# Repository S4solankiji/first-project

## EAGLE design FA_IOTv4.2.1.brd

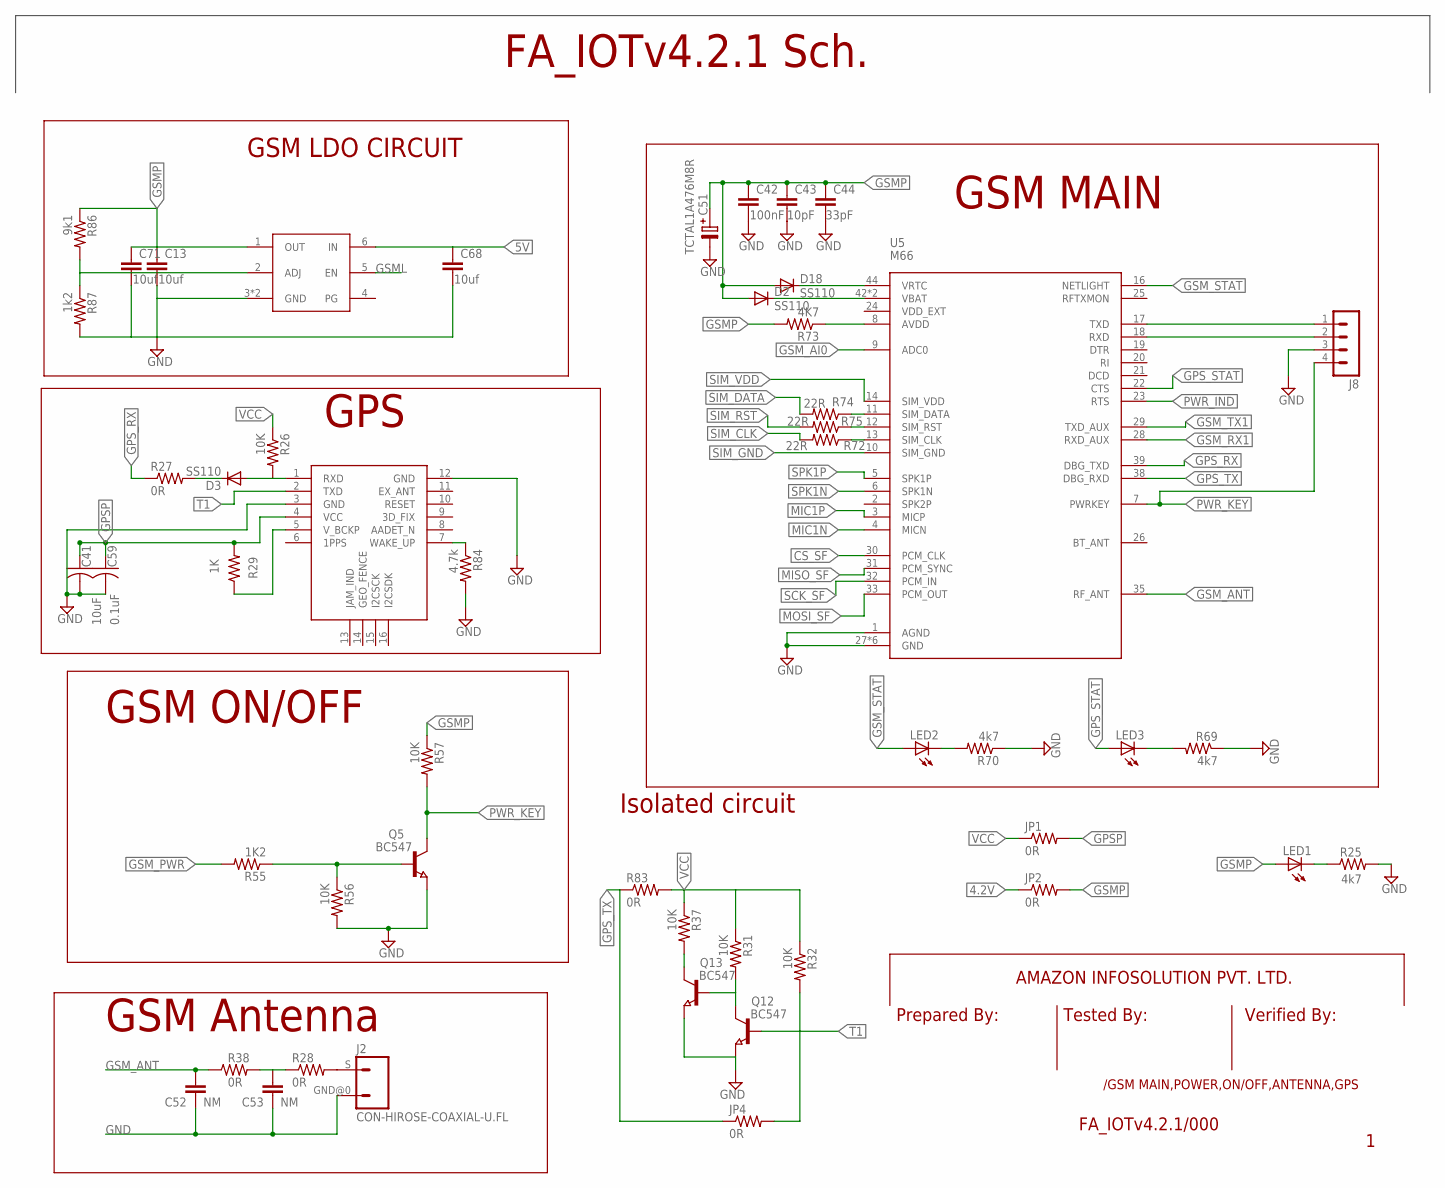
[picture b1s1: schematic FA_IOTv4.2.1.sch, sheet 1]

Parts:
C13, C68, C71: 10uf; C0805
C41: 10uF; C0805
C42: 100nF; C0805
C43: 10pF; C0805
C44: 33pF; C0805
C51: TCTAL1A476M8R; TE-A-3216
C52, C53: NM; C0402
C59: 0.1uF; C0402
D2, D3, D18: SS110; DO-214AC
J2: CON-HIROSE-COAXIAL-U.FL; CON-U.FL
J8: MA04-1
JP1, JP2, JP4: 0R; R0805
LED1, LED2, LED3: LEDCHIP-LED0805; CHIP-LED0805
Q5, Q12, Q13: BC547; SOT23
R25, R69, R70: 4k7; R0402
R26, R31, R32, R37, R56, R57: 10K; R0402
R27, R83: 0R; R0805
R28, R38: 0R; R0402
R29: 1K; R0402
R55: 1K2; R0402
R72, R74, R75: 22R; R0402
R73: 4K7; R0402
R84: 4.7k; R0402
R86: 9k1; R0402
R87: 1k2; R0402
U5: M66
U$1: L89
U$3: LD39200PU33R; SON95P300X300X100-7N

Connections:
4.2V: JP2.1; also elsewhere on the board
5V: C68.1, U$3.6 (IN); also elsewhere on the board
CS_SF: U5.30 (PCM_CLK); also elsewhere on the board
GND: C13.2, C41.2, C42.2, C43.2, C44.2, C51.-, C52.2, C53.2, C59.2, C68.2, C71.2, J2.GND@0 (2), J8.3, Q5.2 (E), Q12.2 (E), Q13.2 (E), R25.2, R56.2, R69.1, R70.1, R84.2, R87.2, U5.1 (AGND), U5.27 (GND), U5.34 (GND), U5.36 (GND), U5.37 (GND), U5.40 (GND), U5.41 (GND), U$1.3 (GND), U$1.12 (GND), U$3.3 (GND), U$3.7 (GND); also elsewhere on the board
GPSP: C41.1, C59.1, JP1.2, R29.2, U$1.4 (VCC); also elsewhere on the board
GPS_RX: R27.1, U5.39 (DBG_TXD)
GPS_STAT: LED3.A, U5.22 (CTS)
GPS_TX: JP4.1, R83.1, U5.38 (DBG_RXD)
GSML: U$3.5 (EN); also elsewhere on the board
GSMP: C13.1, C42.1, C43.1, C44.1, C51.+, C71.1, D2.A, D18.A, JP2.2, LED1.A, R57.1, R73.2, R86.1, U$3.1 (OUT); also elsewhere on the board
GSM_AI0: U5.9 (ADC0); also elsewhere on the board
GSM_ANT: C52.1, R38.1, U5.35 (RF_ANT)
GSM_PWR: R55.2; also elsewhere on the board
GSM_RX1: U5.28 (RXD_AUX); also elsewhere on the board
GSM_STAT: LED2.A, U5.16 (NETLIGHT)
GSM_TX1: U5.29 (TXD_AUX); also elsewhere on the board
MIC1N: U5.4 (MICN); also elsewhere on the board
MIC1P: U5.3 (MICP); also elsewhere on the board
MISO_SF: U5.31 (PCM_SYNC); also elsewhere on the board
MOSI_SF: U5.33 (PCM_OUT); also elsewhere on the board
unnamed: Q13.3 (C), R37.2
unnamed: D2.C, U5.42 (VBAT), U5.43 (VBAT)
unnamed: J2.S (1), R28.2
unnamed: R29.1, U$1.5 (V_BCKP)
unnamed: D3.A, R26.2, U$1.1 (RXD)
unnamed: D3.C, R27.2
unnamed: Q12.3 (C), Q13.1 (B), R31.2
unnamed: Q5.1 (B), R55.1, R56.1
unnamed: R84.1, U$1.7 (WAKE_UP)
unnamed: LED1.C, R25.1
unnamed: LED3.C, R69.2
unnamed: LED2.C, R70.2
unnamed: R73.1, U5.8 (AVDD)
unnamed: R74.1, U5.11 (SIM_DATA)
unnamed: D18.C, U5.44 (VRTC)
unnamed: R75.1, U5.12 (SIM_RST)
unnamed: R72.1, U5.13 (SIM_CLK)
unnamed: R86.2, R87.1, U$3.2 (ADJ)
PWR_IND: U5.23 (RTS); also elsewhere on the board
PWR_KEY: J8.4, Q5.3 (C), R57.2, U5.7 (PWRKEY)
RF_ANT: C53.1, R28.1, R38.2
RX_DEBUG: J8.2, U5.18 (RXD)
SCK_SF: U5.32 (PCM_IN); also elsewhere on the board
SIM_CLK: R72.2; also elsewhere on the board
SIM_DATA: R74.2; also elsewhere on the board
SIM_GND: U5.10 (SIM_GND); also elsewhere on the board
SIM_RST: R75.2; also elsewhere on the board
SIM_VDD: U5.14 (SIM_VDD); also elsewhere on the board
SPK1N: U5.6 (SPK1N); also elsewhere on the board
SPK1P: U5.5 (SPK1P); also elsewhere on the board
T1: JP4.2, Q12.1 (B), R32.2, U$1.2 (TXD)
TX_DEBUG: J8.1, U5.17 (TXD)
VCC: JP1.1, R26.1, R31.1, R32.1, R37.1, R83.2; also elsewhere on the board

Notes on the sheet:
GSM ON/OFF
GPS
GSM MAIN
GSM Antenna
AMAZON INFOSOLUTION PVT. LTD.
Prepared By:
Tested By:
Verified By:
/GSM MAIN,POWER,ON/OFF,ANTENNA,GPS
FA_IOTv4.2.1/000
FA_IOTv4.2.1 Sch.
GSM LDO CIRCUIT
Isolated circuit

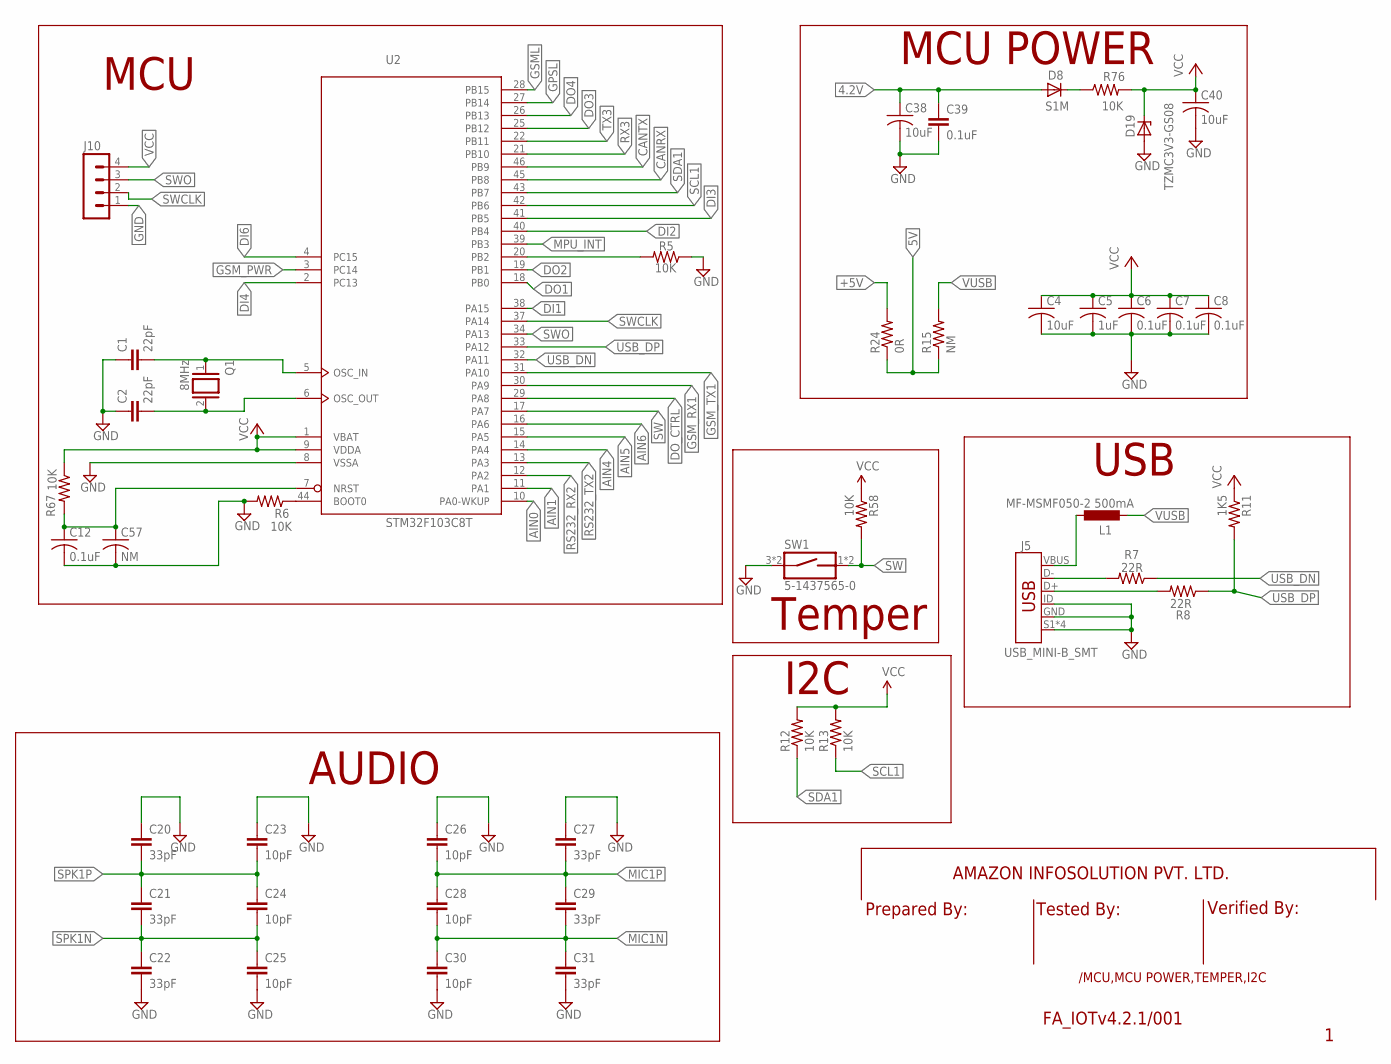
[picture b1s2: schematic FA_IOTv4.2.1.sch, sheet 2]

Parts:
C1, C2: 22pF; C0201
C4, C38, C40: 10uF; C0805
C5: 1uF; C0603
C6, C7, C8, C12: 0.1uF; C0402
C20, C21, C22, C27, C29, C31: 33pF; C0402
C23, C24, C25, C26, C28, C30: 10pF; C0402
C39: 0.1uF; C0805
C57: NM; C0402
D8: S1M; DO-214AC
D19: TZMC3V3-GS08; SOD80C
J5: USB_MINI-B_SMT; USB-MINIB
J10: MA04-1
L1: MF-MSMF050-2 500mA; L1812
Q1: 8MHz; QS
R5, R6, R58, R67: 10K; R0402
R7, R8: 22R; R0402
R11: 1K5; R0402
R12, R13: 10K; 0603-RES
R15: NM; R0805
R24: 0R; R0805
R76: 10K; R0805
SW1: 5-1437565-0; SW_5-1437565-0
U2: STM32F103C8T; LQFP48

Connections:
4.2V: C38.1, C39.1, D8.A; also elsewhere on the board
5V: R15.1, R24.1; also elsewhere on the board
+5V: R24.2; also elsewhere on the board
AIN0: U2.10 (PA0-WKUP); also elsewhere on the board
AIN1: U2.11 (PA1); also elsewhere on the board
AIN4: U2.14 (PA4); also elsewhere on the board
AIN5: U2.15 (PA5)
AIN6: U2.16 (PA6)
CANRX: U2.45 (PB8); also elsewhere on the board
CANTX: U2.46 (PB9); also elsewhere on the board
DI1: U2.38 (PA15); also elsewhere on the board
DI2: U2.40 (PB4); also elsewhere on the board
DI3: U2.41 (PB5); also elsewhere on the board
DI4: U2.2 (PC13)
DI6: U2.4 (PC15); also elsewhere on the board
DO1: U2.18 (PB0); also elsewhere on the board
DO2: U2.19 (PB1); also elsewhere on the board
DO3: U2.25 (PB12); also elsewhere on the board
DO4: U2.26 (PB13); also elsewhere on the board
DO_CTRL: U2.29 (PA8)
GND: C1.1, C2.1, C4.2, C5.2, C6.2, C7.2, C8.2, C12.2, C20.1, C22.2, C23.1, C25.2, C26.1, C27.1, C30.2, C31.2, C38.2, C39.2, C40.2, C57.2, D19.A, J5.GND, J5.ID, J5.S1 (SHIELD), J5.S2 (SHIELD), J5.S3 (SHIELD), J5.S4 (SHIELD), J10.1, R5.1, R6.2, SW1.3 (1), SW1.4 (1), U2.8 (VSSA), U2.23 (GND), U2.35 (GND), U2.47 (GND); also elsewhere on the board
GPSL: U2.27 (PB14); also elsewhere on the board
GSML: U2.28 (PB15); also elsewhere on the board
GSM_PWR: U2.3 (PC14); also elsewhere on the board
GSM_RX1: U2.30 (PA9); also elsewhere on the board
GSM_TX1: U2.31 (PA10); also elsewhere on the board
MIC1N: C28.2, C29.2, C30.1, C31.1; also elsewhere on the board
MIC1P: C26.2, C27.2, C28.1, C29.1; also elsewhere on the board
MPU_INT: U2.39 (PB3); also elsewhere on the board
unnamed: C1.2, Q1.1, U2.5 (OSC_IN)
unnamed: C2.2, Q1.2, U2.6 (OSC_OUT)
unnamed: R6.1, U2.44 (BOOT0)
unnamed: R5.2, U2.20 (PB2)
unnamed: J5.D-, R7.2
unnamed: J5.D+, R8.2
unnamed: J5.VBUS, L1.1
unnamed: D8.C, R76.1
unnamed: C12.1, C57.1, R67.2, U2.7 (NRST)
RS232_RX2: U2.12 (PA2); also elsewhere on the board
RS232_TX2: U2.13 (PA3); also elsewhere on the board
RX3: U2.21 (PB10); also elsewhere on the board
SCL1: R13.1, U2.42 (PB6); also elsewhere on the board
SDA1: R12.1, U2.43 (PB7); also elsewhere on the board
SPK1N: C21.2, C22.1, C24.2, C25.1; also elsewhere on the board
SPK1P: C20.2, C21.1, C23.2, C24.1; also elsewhere on the board
SW: R58.2, SW1.1 (2), SW1.2, U2.17 (PA7)
SWCLK: J10.2, U2.37 (PA14)
SWO: J10.3, U2.34 (PA13)
TX3: U2.22 (PB11); also elsewhere on the board
USB_DN: R7.1, U2.32 (PA11)
USB_DP: R8.1, R11.2, U2.33 (PA12)
VCC: C4.1, C5.1, C6.1, C7.1, C8.1, C40.1, D19.C, J10.4, R11.1, R12.2, R13.2, R58.1, R67.1, R76.2, U2.1 (VBAT), U2.9 (VDDA), U2.24 (VCC), U2.36 (VCC), U2.48 (VCC); also elsewhere on the board
VUSB: L1.2, R15.2

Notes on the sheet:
MCU
MCU POWER
USB
I2C
Temper
AUDIO
AMAZON INFOSOLUTION PVT. LTD.
Prepared By:
Tested By:
Verified By:
/MCU,MCU POWER,TEMPER,I2C
FA_IOTv4.2.1/001

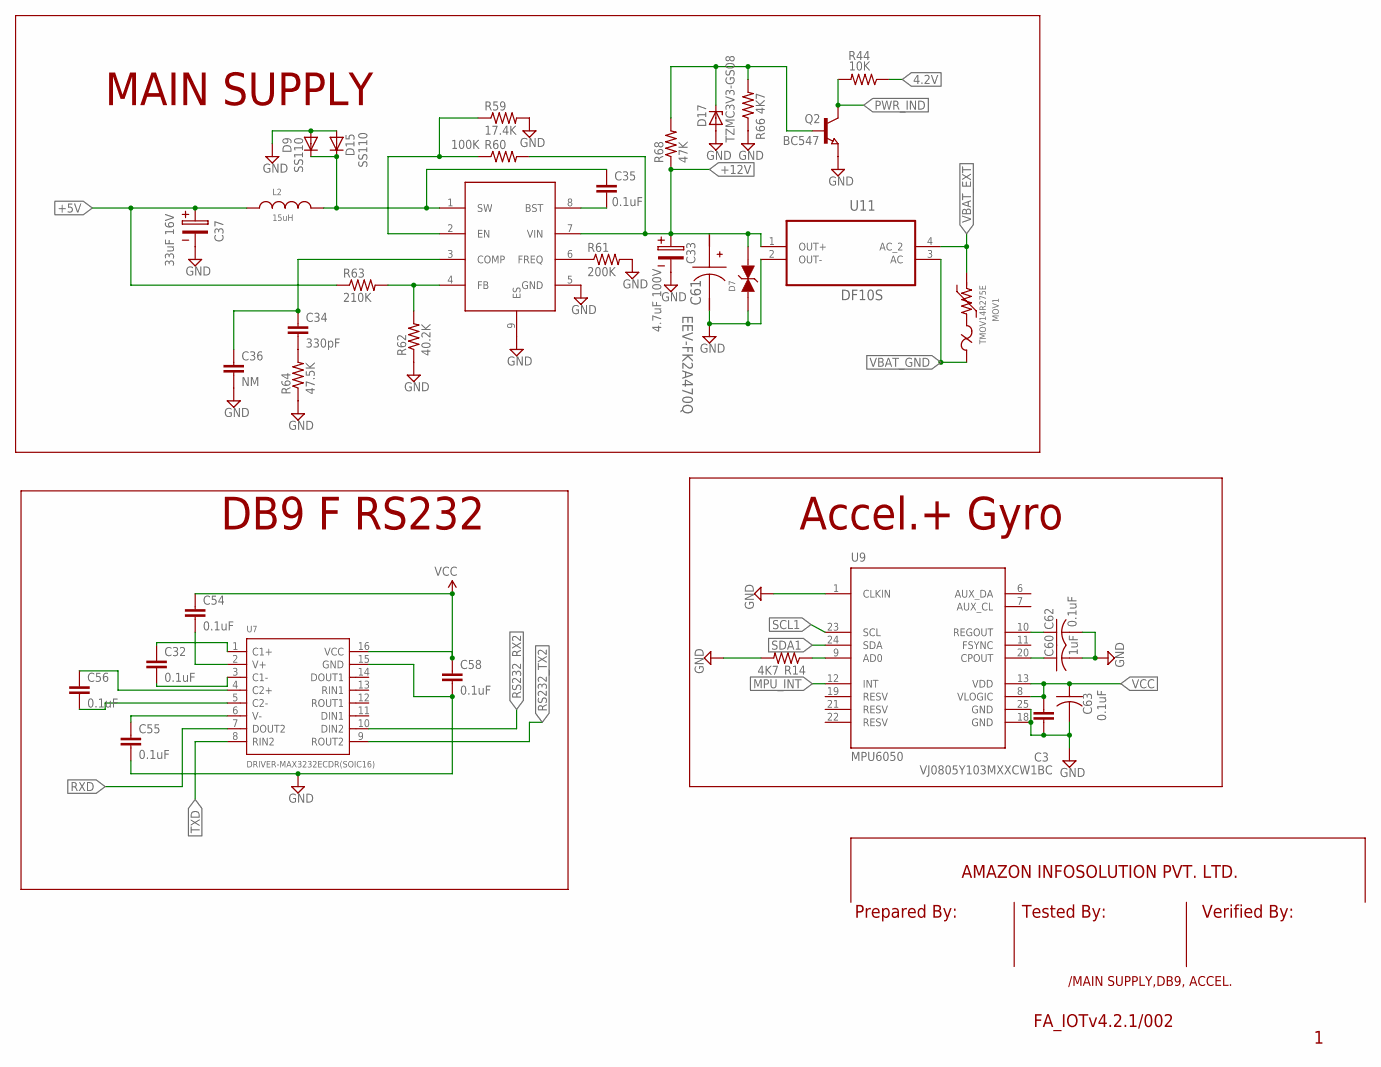
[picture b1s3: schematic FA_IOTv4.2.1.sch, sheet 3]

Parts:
C3: VJ0805Y103MXXCW1BC; C0805
C32, C54, C55, C56, C58, C62, C63: 0.1uF; C0402
C33: 4.7uF 100V; 3.5X1.6X2.1(BXCXA)
C34: 330pF; C0805
C35: 0.1uF; C0805
C36: NM; C0805
C37: 33uF 16V; 3.5X1.6X2.1(BXCXA)
C60: 1uF; C0603
C61: EEV-FK2A470Q; SM_RADIAL_H13
D7: WE-TVSP_BI_1500W_824541331; VARTVSP_SMC&SMD/DO-214AB
D9, D15: SS110; DO-214AC
D17: TZMC3V3-GS08; SOD80C
L2: 15uH; WE-PD_1260/1245/1280/1210
MOV1: TMOV14R275E
Q2: BC547; SOT23
R14: 4K7; R0402
R44: 10K; R0805
R59: 17.4K; R0805
R60: 100K; R0805
R61: 200K; R0805
R62: 40.2K; R0805
R63: 210K; R0805
R64: 47.5K; R0805
R66: 4K7; R0805
R68: 47K; R0805
U7: DRIVER-MAX3232ECDR(SOIC16); SOIC16-1.27-10X3.9MM
U9: MPU6050; QFN50P400X400X95-25T265X275N
U10: MP4559DN; SOIC127P600X170-9N
U11: DF10S; SOT508P985X260-4N

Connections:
4.2V: R44.1; also elsewhere on the board
+5V: C37.1, L2.1, R63.1; also elsewhere on the board
+12V: C33.1, C61.1 (+), D7.2, R60.2, R68.1, U10.7 (VIN), U11.1 (OUT+); also elsewhere on the board
GND: C3.2, C33.2, C36.2, C37.2, C55.2, C58.2, C60.2, C61.2 (-), C62.2, C63.2, D7.1, D9.A, D15.A, D17.A, Q2.2 (E), R14.2, R59.2, R61.2, R62.1, R64.1, R66.1, U7.15 (GND), U9.1 (CLKIN), U9.18 (GND), U9.25 (GND), U10.5 (GND), U10.9 (ES), U11.2 (OUT-); also elsewhere on the board
MPU_INT: U9.12 (INT); also elsewhere on the board
unnamed: C35.1, D9.C, D15.C, L2.2, U10.1 (SW)
unnamed: R14.1, U9.9 (AD0)
unnamed: C62.1, U9.10 (REGOUT)
unnamed: C32.1, U7.1 (C1+)
unnamed: C32.2, U7.3 (C1-)
unnamed: C60.1, U9.20 (CPOUT)
unnamed: R59.1, R60.1, U10.2 (EN)
unnamed: C34.2, R64.2
unnamed: R61.1, U10.6 (FREQ)
unnamed: R62.2, R63.2, U10.4 (FB)
unnamed: C34.1, C36.1, U10.3 (COMP)
unnamed: C35.2, U10.8 (BST)
unnamed: D17.C, Q2.1 (B), R66.2, R68.2
unnamed: C54.2, U7.2 (V+)
unnamed: C56.1, U7.4 (C2+)
unnamed: C56.2, U7.5 (C2-)
unnamed: C55.1, U7.6 (V-)
PWR_IND: Q2.3 (C), R44.2; also elsewhere on the board
RS232_RX2: U7.10 (DIN2); also elsewhere on the board
RS232_TX2: U7.9 (ROUT2); also elsewhere on the board
RXD: U7.7 (DOUT2); also elsewhere on the board
SCL1: U9.23 (SCL); also elsewhere on the board
SDA1: U9.24 (SDA); also elsewhere on the board
TXD: U7.8 (RIN2); also elsewhere on the board
VBAT_EXT: MOV1.2 (MOV), U11.4 (AC_2); also elsewhere on the board
VBAT_GND: MOV1.1 (FUSE), U11.3 (AC); also elsewhere on the board
VCC: C3.1, C54.1, C58.1, C63.1, U7.16 (VCC), U9.8 (VLOGIC), U9.13 (VDD); also elsewhere on the board

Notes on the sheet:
MAIN SUPPLY
DB9 F RS232
Accel.+ Gyro
AMAZON INFOSOLUTION PVT. LTD.
Prepared By:
Tested By:
Verified By:
/MAIN SUPPLY,DB9, ACCEL.
FA_IOTv4.2.1/002

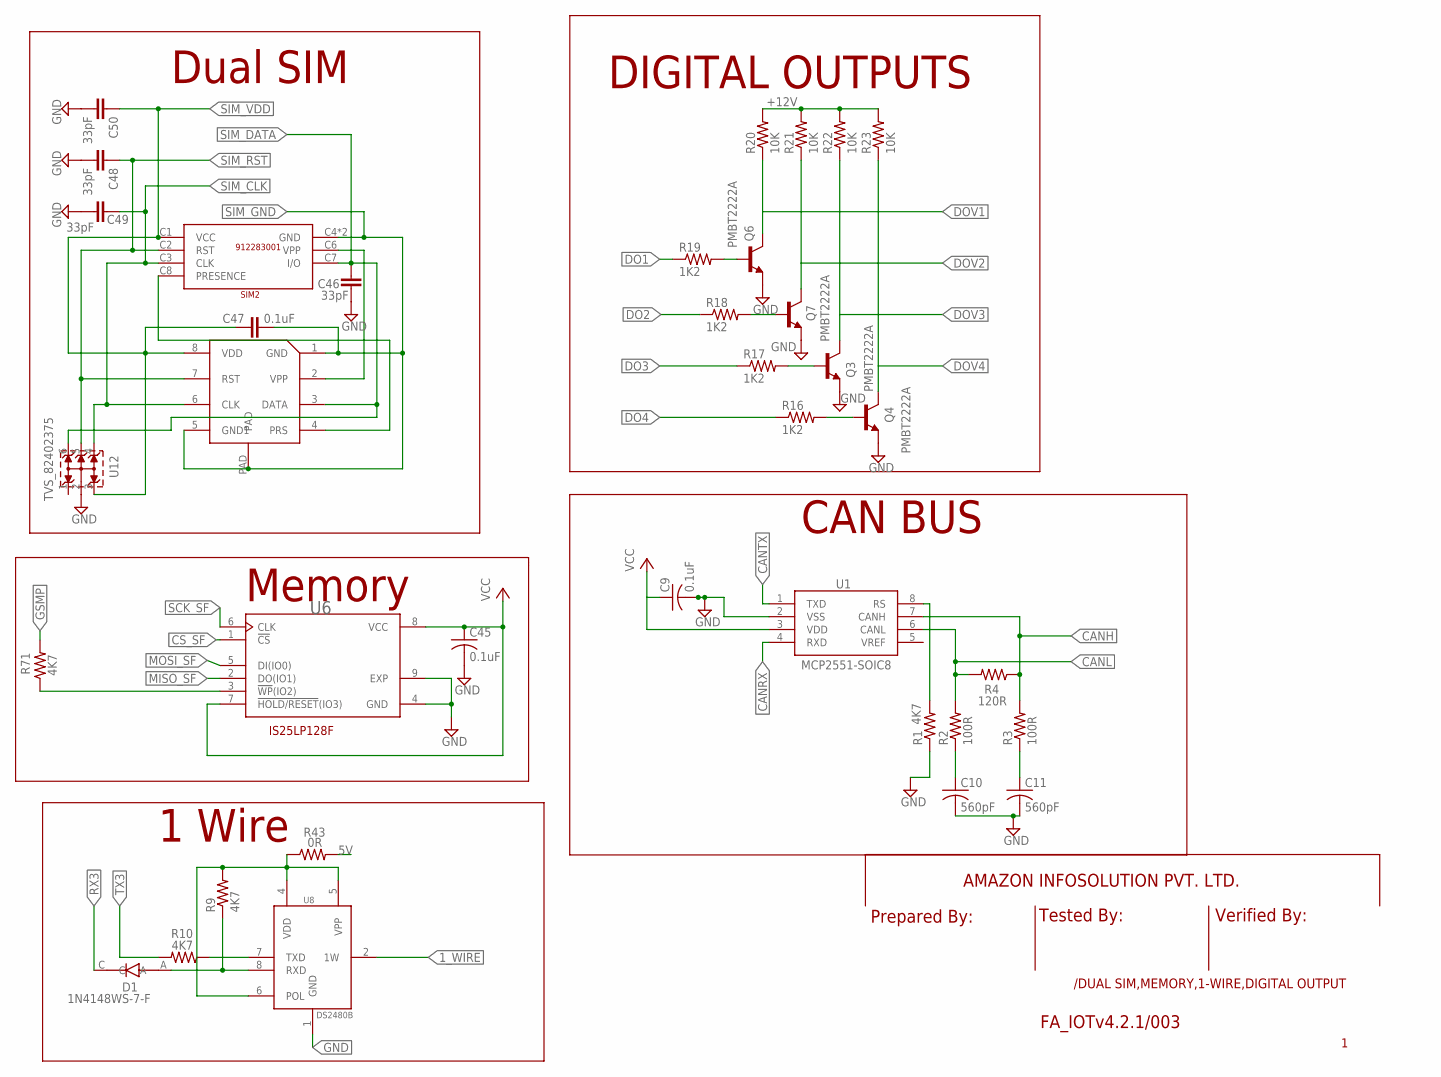
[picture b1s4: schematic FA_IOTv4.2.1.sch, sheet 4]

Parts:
C9, C47: 0.1uF; C0805
C10, C11: 560pF; C0402
C45: 0.1uF; C0402
C46, C48, C49, C50: 33pF; C0805
D1: 1N4148WS-7-F; SOD2513X120N
Q3, Q4, Q6, Q7: PMBT2222A; SOT23-BEC
R1, R9, R10, R71: 4K7; R0402
R2, R3: 100R; R0402
R4: 120R; R0402
R16, R17, R18, R19: 1K2; R0402
R20, R21, R22, R23: 10K; R0805
R43: 0R; R0805
SIM1: MFF2_SIM; MFF2DFN8
SIM2: 912283001; 91228-3001
U1: MCP2551-SOIC8; SOIC8-6.0
U6: W25Q32FVZPIG_TR; SON127P600X500X80-9N
U8: DS2480B; SO08
U12: TVS_82402375; WE-TVS_SC70-6L

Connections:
1_WIRE: U8.2 (1W); also elsewhere on the board
5V: R43.2; also elsewhere on the board
+12V: R20.2, R21.2, R22.2, R23.2; also elsewhere on the board
CANH: R3.2, R4.1, U1.7 (CANH); also elsewhere on the board
CANL: R2.2, R4.2, U1.6 (CANL); also elsewhere on the board
CANRX: U1.4 (RXD); also elsewhere on the board
CANTX: U1.1 (TXD); also elsewhere on the board
CS_SF: U6.1 (!CS); also elsewhere on the board
DO1: R19.1; also elsewhere on the board
DO2: R18.1; also elsewhere on the board
DO3: R17.1; also elsewhere on the board
DO4: R16.1; also elsewhere on the board
DOV1: Q6.C, R20.1; also elsewhere on the board
DOV2: Q7.C, R21.1; also elsewhere on the board
DOV3: Q3.C, R22.1; also elsewhere on the board
DOV4: Q4.C, R23.1; also elsewhere on the board
GND: C9.2, C10.2, C11.2, C45.2, C46.2, C48.2, C49.2, C50.2, Q3.E, Q4.E, Q6.E, Q7.E, R1.1, U1.2 (VSS), U6.4 (GND), U6.9 (EXP), U8.1 (GND), U12.2 (GND); also elsewhere on the board
GSMP: R71.2; also elsewhere on the board
MISO_SF: U6.2 (DO(IO1)); also elsewhere on the board
MOSI_SF: U6.5 (DI(IO0)); also elsewhere on the board
unnamed: C10.1, R2.1
unnamed: C11.1, R3.1
unnamed: R1.2, U1.8 (RS)
unnamed: R10.1, U8.7 (TXD)
unnamed: D1.A, R9.1, U8.8 (RXD)
unnamed: Q6.B, R19.2
unnamed: Q7.B, R18.2
unnamed: Q3.B, R17.2
unnamed: Q4.B, R16.2
unnamed: R9.2, R43.1, U8.4 (VDD), U8.5 (VPP), U8.6 (POL)
unnamed: R71.1, U6.3 (!WP!(IO2))
unnamed: SIM1.4 (PRS), SIM2.C8 (PRESENCE)
unnamed: SIM1.2 (VPP), SIM2.C6 (VPP)
RX3: D1.C; also elsewhere on the board
SCK_SF: U6.6 (CLK); also elsewhere on the board
SIM_CLK: C49.1, SIM1.6 (CLK), SIM2.C3 (CLK), U12.4 (3); also elsewhere on the board
SIM_DATA: C46.1, SIM1.3 (DATA), SIM2.C7 (I/O), U12.6 (5); also elsewhere on the board
SIM_GND: C47.2, SIM1.1 (GND), SIM1.5 (GND1), SIM1.PAD, SIM2.C4 (GND), SIM2.C5 (GND); also elsewhere on the board
SIM_RST: C48.1, SIM1.7 (RST), SIM2.C2 (RST), U12.5 (4); also elsewhere on the board
SIM_VDD: C47.1, C50.1, SIM1.8 (VDD), SIM2.C1 (VCC), U12.3 (2); also elsewhere on the board
TX3: R10.2; also elsewhere on the board
VCC: C9.1, C45.1, U1.3 (VDD), U6.7 (!HOLD/RESET!(IO3)), U6.8 (VCC); also elsewhere on the board

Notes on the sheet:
Dual SIM
DIGITAL OUTPUTS
CAN BUS
Memory
1 Wire
AMAZON INFOSOLUTION PVT. LTD.
Prepared By:
Tested By:
Verified By:
/DUAL SIM,MEMORY,1-WIRE,DIGITAL OUTPUT
FA_IOTv4.2.1/003
IS25LP128F

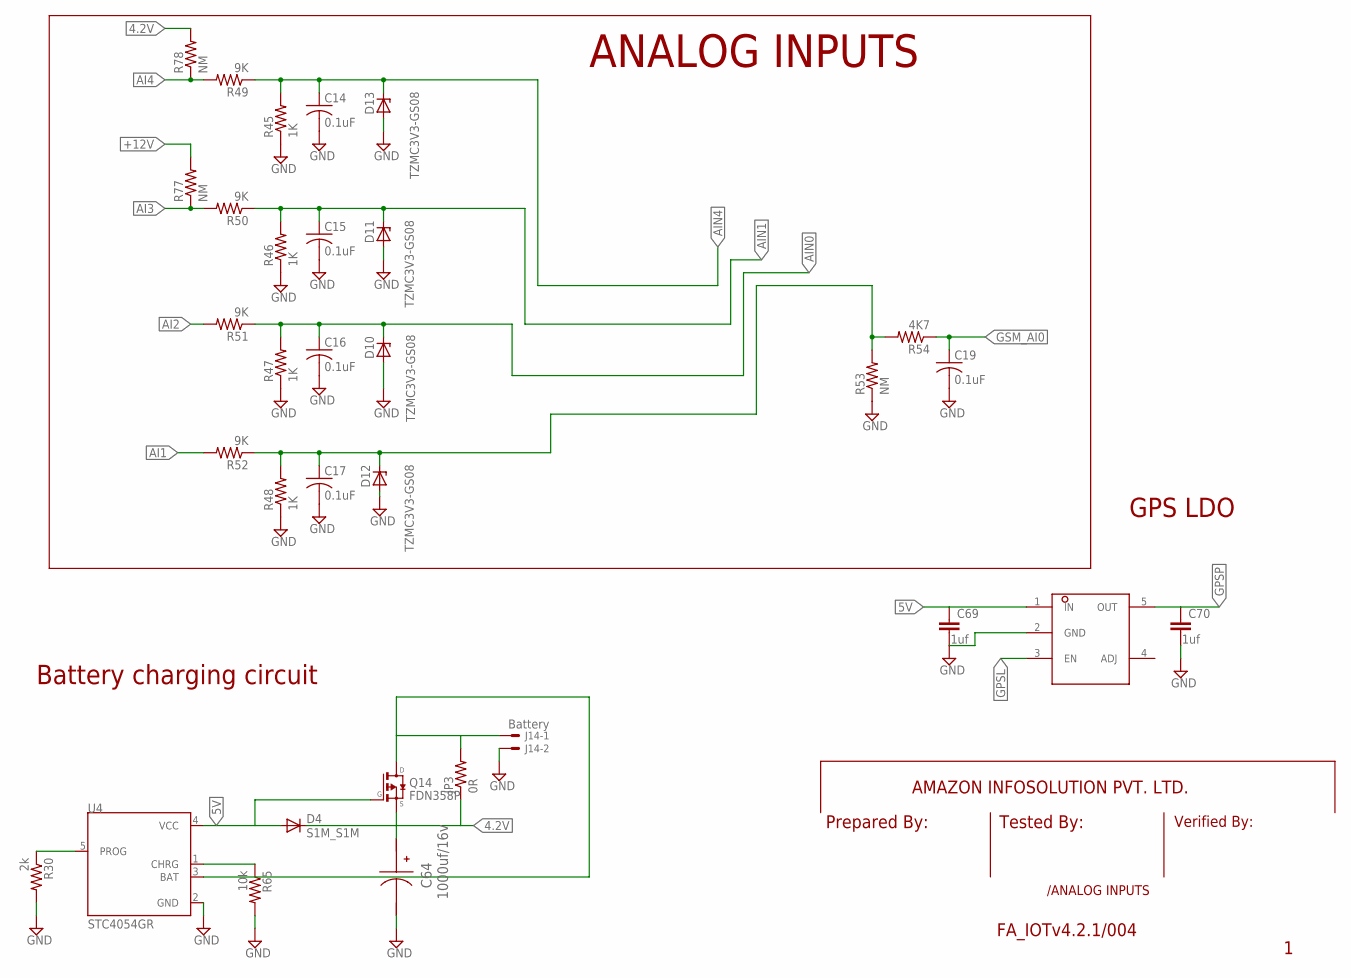
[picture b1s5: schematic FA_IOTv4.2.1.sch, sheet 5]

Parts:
C14, C15, C16, C17, C19: 0.1uF; C0402
C64: 1000uf/16v; SM_RADIAL_H13
C69, C70: 1uf; C0603
D4: S1M_S1M; S1M_DO-214AC
D10, D11, D12, D13: TZMC3V3-GS08; SOD80C
J14: Battery; 6410-02
JP3: 0R; R0805
Q14: FDN358P; SSOT-3
R30: 2k; R0402
R45, R46, R47, R48: 1K; R0402
R49, R50, R51, R52: 9K; R0402
R53: NM; R0402
R54: 4K7; R0402
R65: 10k; R0402
R77, R78: NM; R0805
U4: STC4054GR; SOT95P280X110-5N
U$4: LDK220M33R; SOT95P280X145-5N

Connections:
4.2V: C64.1 (+), D4.C, JP3.1, Q14.2 (S), R78.2; also elsewhere on the board
5V: C69.1, D4.A, Q14.1 (G), U4.4 (VCC), U$4.1 (IN); also elsewhere on the board
+12V: R77.2; also elsewhere on the board
AI1: R52.2; also elsewhere on the board
AI2: R51.2; also elsewhere on the board
AI3: R50.2, R77.1; also elsewhere on the board
AI4: R49.2, R78.1; also elsewhere on the board
AIN0: C16.1, D10.C, R47.2, R51.1; also elsewhere on the board
AIN1: C15.1, D11.C, R46.2, R50.1; also elsewhere on the board
AIN4: C14.1, D13.C, R45.2, R49.1; also elsewhere on the board
FB4: C17.1, D12.C, R48.2, R52.1, R53.2, R54.2
GND: C14.2, C15.2, C16.2, C17.2, C19.2, C64.2 (-), C69.2, C70.2, D10.A, D11.A, D12.A, D13.A, J14.2, R30.2, R45.1, R46.1, R47.1, R48.1, R53.1, R65.2, U4.2 (GND), U$4.2 (GND); also elsewhere on the board
GPSL: U$4.3 (EN); also elsewhere on the board
GPSP: C70.1, U$4.5 (OUT); also elsewhere on the board
GSM_AI0: C19.1, R54.1; also elsewhere on the board
unnamed: J14.1, JP3.2, Q14.3 (D), U4.3 (BAT)
unnamed: R65.1, U4.1 (CHRG)
unnamed: R30.1, U4.5 (PROG)

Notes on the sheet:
ANALOG INPUTS
AMAZON INFOSOLUTION PVT. LTD.
Prepared By:
Tested By:
Verified By:
/ANALOG INPUTS
FA_IOTv4.2.1/004
Battery charging circuit
GPS LDO

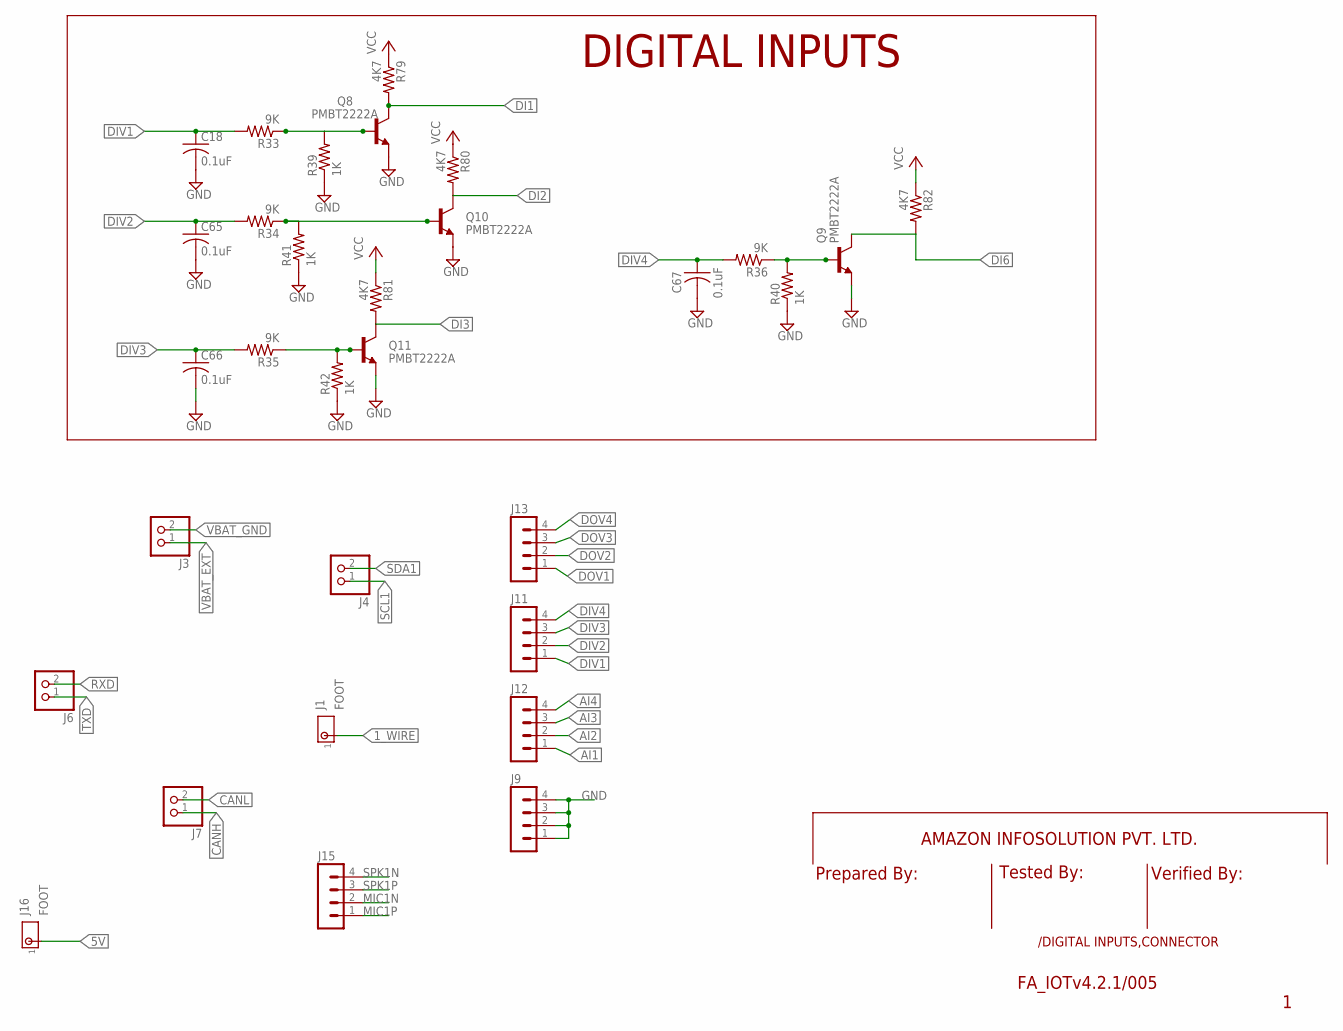
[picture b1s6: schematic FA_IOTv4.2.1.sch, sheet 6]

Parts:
C18, C65, C66, C67: 0.1uF; C0402
J1, J16: FOOT
J3, J4, J6, J7: PINHD-1X2; 1X02
J9, J11, J12, J13, J15: MA04-1
Q8, Q9, Q10, Q11: PMBT2222A; SOT23-BEC
R33, R34, R35, R36: 9K; R0402
R39, R40, R41, R42: 1K; R0402
R79, R80, R81, R82: 4K7; R0402

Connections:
1_WIRE: J1.1; also elsewhere on the board
5V: J16.1; also elsewhere on the board
AI1: J12.1; also elsewhere on the board
AI2: J12.2; also elsewhere on the board
AI3: J12.3; also elsewhere on the board
AI4: J12.4; also elsewhere on the board
CANH: J7.1; also elsewhere on the board
CANL: J7.2; also elsewhere on the board
DI1: Q8.C, R79.2; also elsewhere on the board
DI2: Q10.C, R80.2; also elsewhere on the board
DI3: Q11.C, R81.2; also elsewhere on the board
DI6: Q9.C, R82.2; also elsewhere on the board
DIV1: C18.1, J11.1, R33.2
DIV2: C65.1, J11.2, R34.2
DIV3: C66.1, J11.3, R35.2
DIV4: C67.1, J11.4, R36.2
DOV1: J13.1; also elsewhere on the board
DOV2: J13.2; also elsewhere on the board
DOV3: J13.3; also elsewhere on the board
DOV4: J13.4; also elsewhere on the board
GND: C18.2, C65.2, C66.2, C67.2, J9.1, J9.2, J9.3, J9.4, Q8.E, Q9.E, Q10.E, Q11.E, R39.1, R40.1, R41.1, R42.1; also elsewhere on the board
MIC1N: J15.2; also elsewhere on the board
MIC1P: J15.1; also elsewhere on the board
unnamed: Q8.B, R33.1, R39.2
unnamed: Q9.B, R36.1, R40.2
unnamed: Q10.B, R34.1, R41.2
unnamed: Q11.B, R35.1, R42.2
RXD: J6.2; also elsewhere on the board
SCL1: J4.1; also elsewhere on the board
SDA1: J4.2; also elsewhere on the board
SPK1N: J15.4; also elsewhere on the board
SPK1P: J15.3; also elsewhere on the board
TXD: J6.1; also elsewhere on the board
VBAT_EXT: J3.1; also elsewhere on the board
VBAT_GND: J3.2; also elsewhere on the board
VCC: R79.1, R80.1, R81.1, R82.1; also elsewhere on the board

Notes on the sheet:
DIGITAL INPUTS
AMAZON INFOSOLUTION PVT. LTD.
Prepared By:
Tested By:
Verified By:
/DIGITAL INPUTS,CONNECTOR
FA_IOTv4.2.1/005

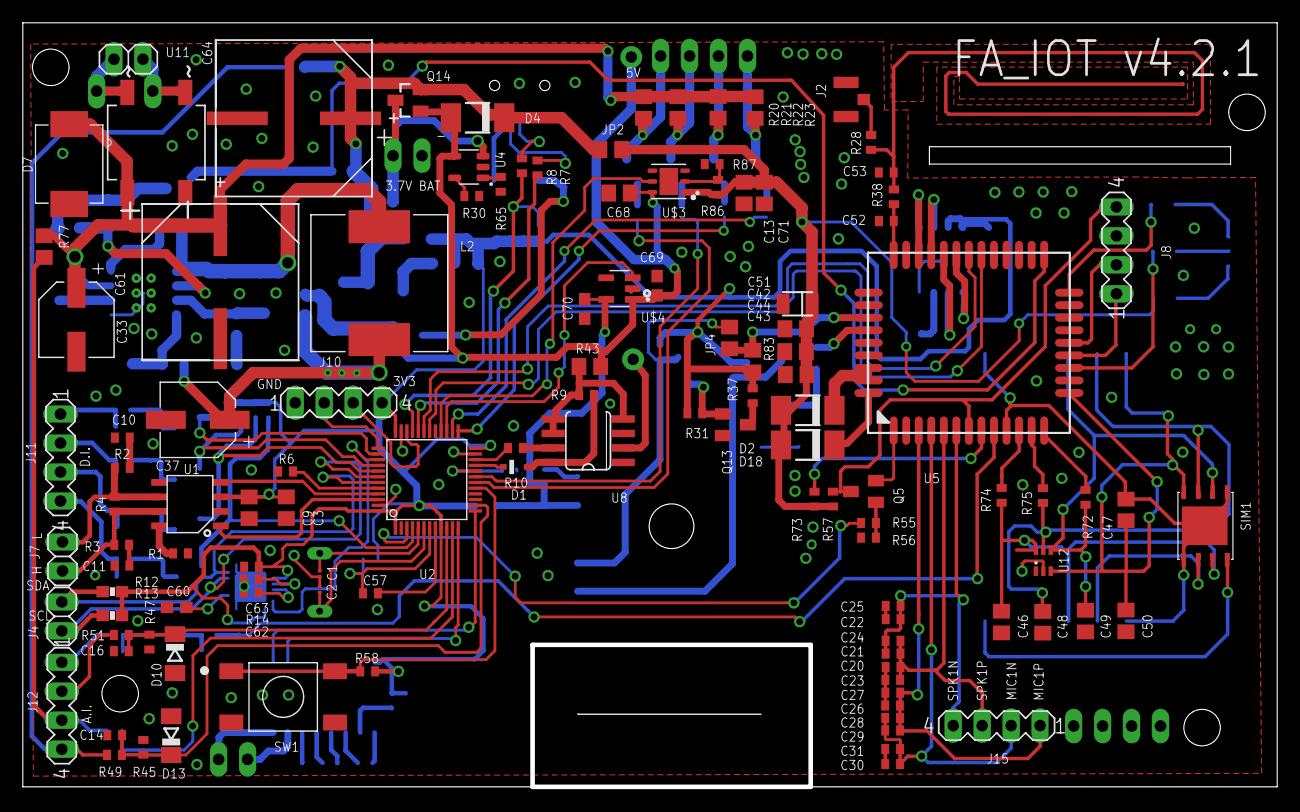
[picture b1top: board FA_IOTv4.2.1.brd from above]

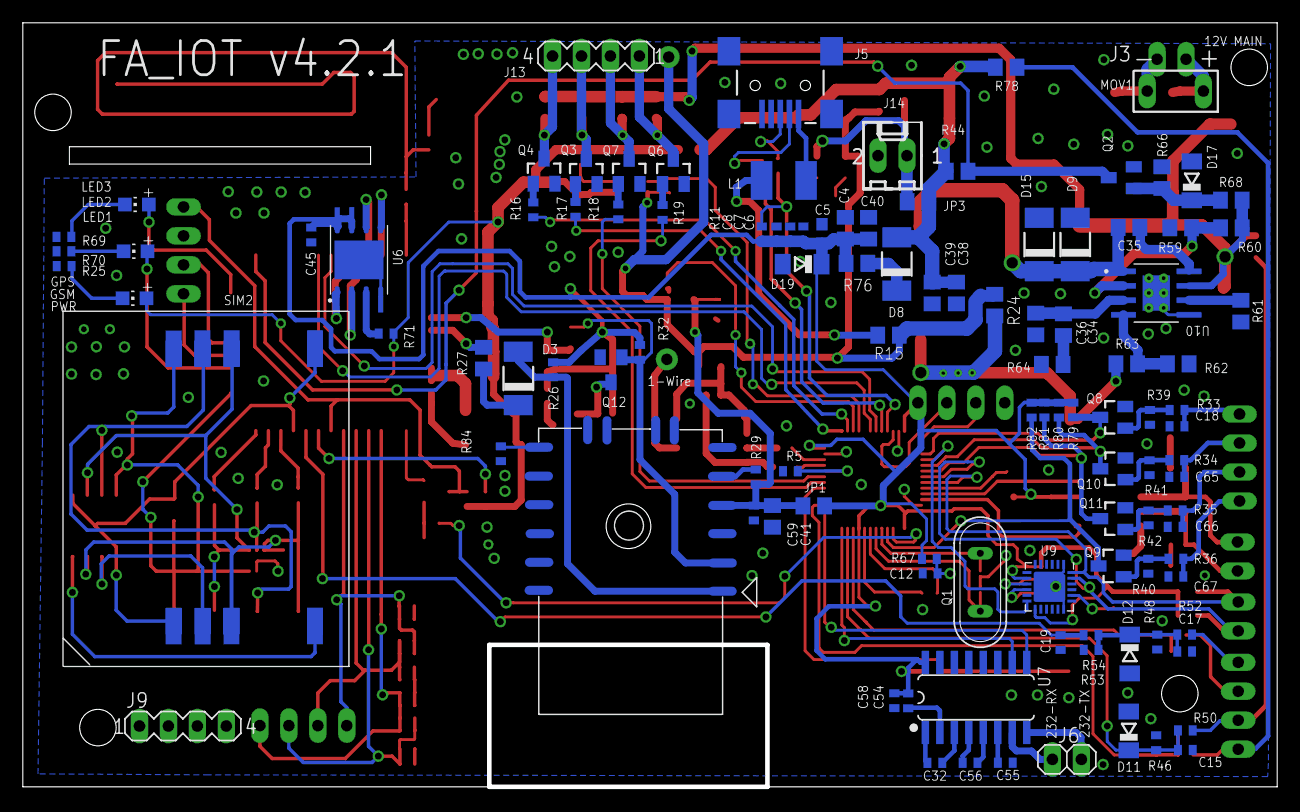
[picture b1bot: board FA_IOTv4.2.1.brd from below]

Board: 2 copper layers, 109.6 x 66.8 mm, 229 parts (112 on the bottom side), 148 nets.

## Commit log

2021-09-01 first eagle files
2021-09-01 hello ji

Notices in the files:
parts and their libraries:
SparkFun-Connectors: Licensing: Creative Commons ShareAlike 4.0 International - https://creativecommons.org/licenses/by-sa/4.0
WE_PowerMagnetics: Copyright: Würth Elektronik
cap-pan40: Copyright (C) 2004, Bob Starr
m-pad-2.1: License : GNU General Public License version 2 (see bottom)
